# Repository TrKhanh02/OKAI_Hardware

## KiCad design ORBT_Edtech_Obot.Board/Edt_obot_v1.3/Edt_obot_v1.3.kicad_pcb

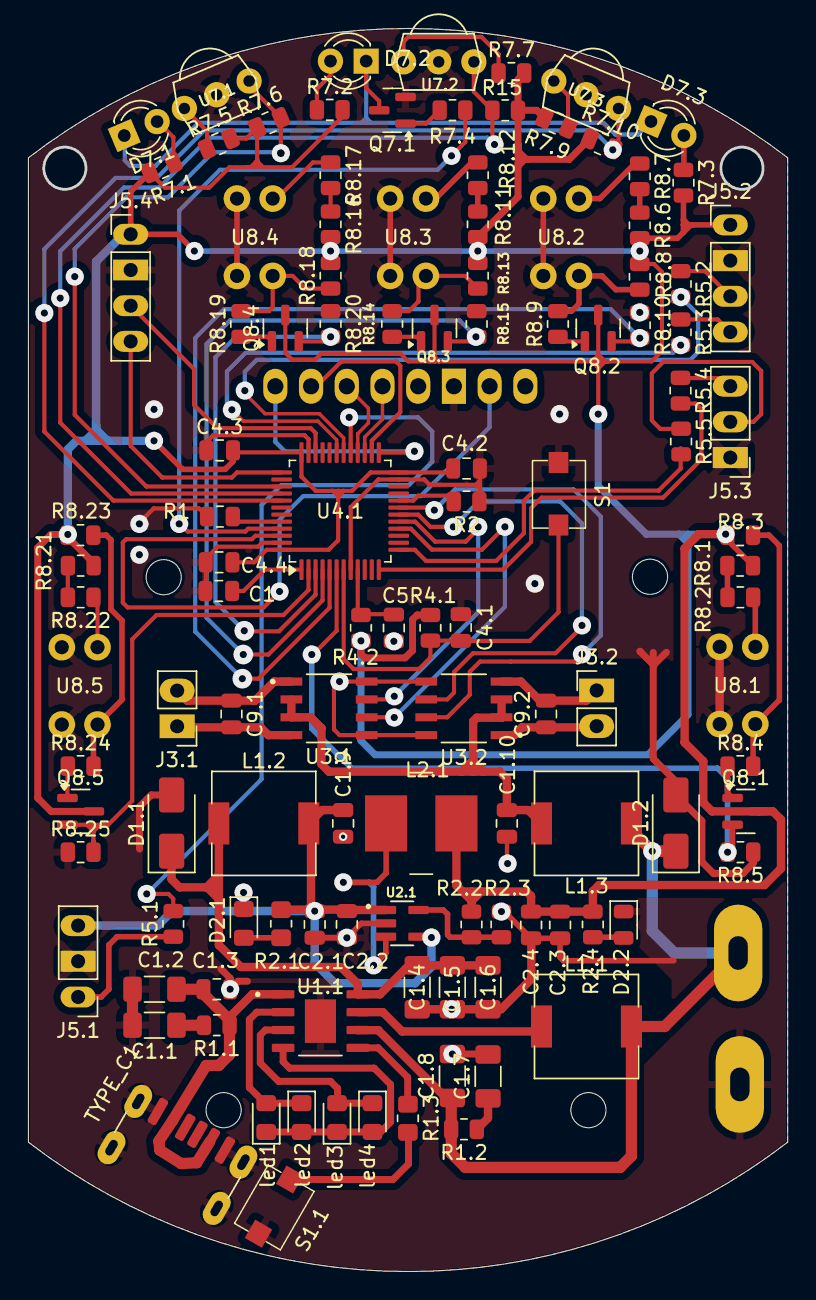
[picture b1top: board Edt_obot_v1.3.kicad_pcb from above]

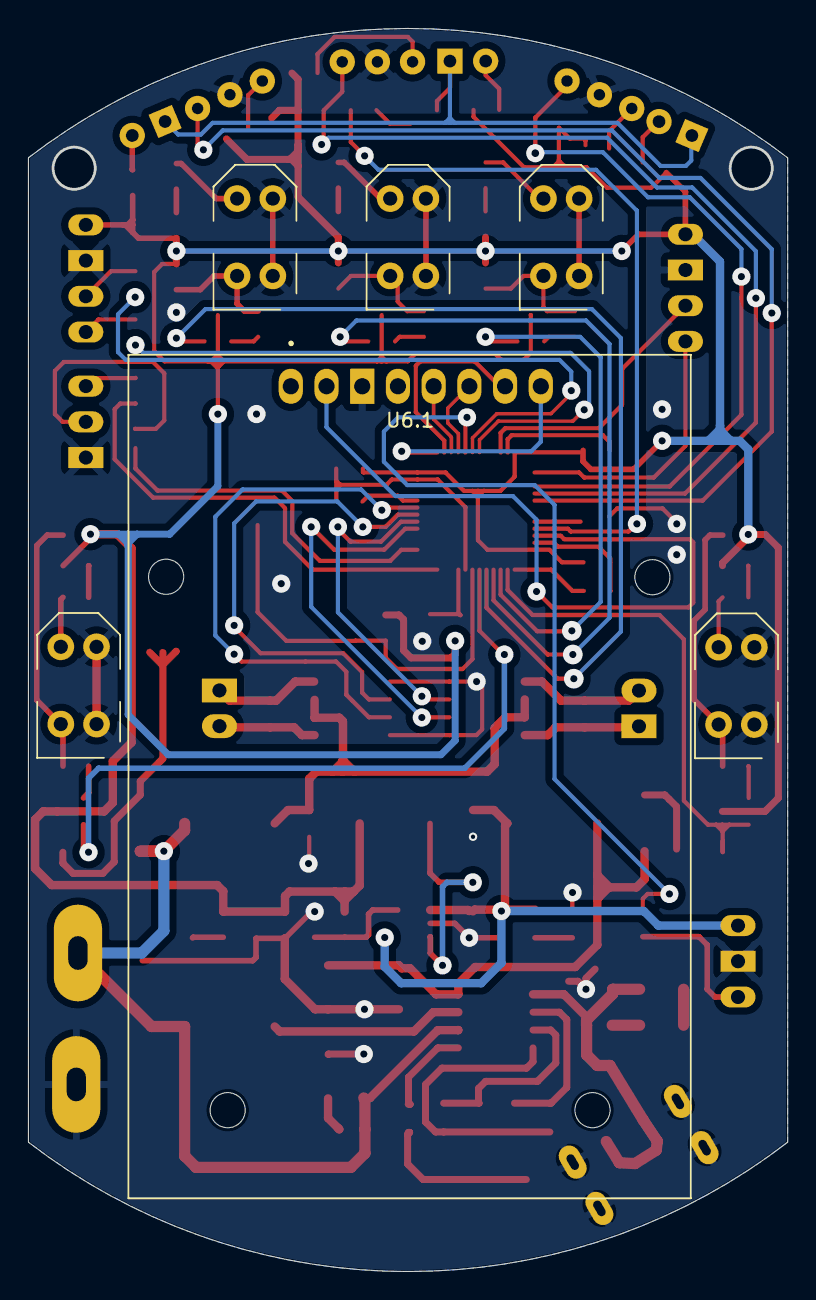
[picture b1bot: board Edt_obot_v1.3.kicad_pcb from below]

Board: 2 copper layers, 54.0 x 88.4 mm, 117 parts (6 on the bottom side), 86 nets.

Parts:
C1, C1.3, C4.1, C4.2, C4.3, C4.4, C5, C9.1, C9.2: 104; C_0805_2012Metric
C1.1, C1.2: 106; C_1206_3216Metric_Pad1.33x1.80mm_HandSolder
C1.4, C1.5, C1.6: 22 UF; C_1206_3216Metric_Pad1.33x1.80mm_HandSolder
C1.7: 22uf; C_1206_3216Metric_Pad1.33x1.80mm_HandSolder
C1.8: 22uF; C_1206_3216Metric_Pad1.33x1.80mm_HandSolder
C1.9, C1.10, C2.1, C2.4: 10uF; C_0805_2012Metric
C2.2, C2.3: 0.1uF; C_0805_2012Metric
D1.1, D1.2: SS34; D_SMA
D2.1: LED_Small_Filled; LED_0805_2012Metric_Pad1.15x1.40mm_HandSolder
D2.2: LED; LED_0805_2012Metric
D7.1, D7.2, D7.3: IR7393C; LED_D3.0mm_IRBlack
J3.1: MT1; PinHeader_1x02_P2.54mm_Vertical
J3.2: MT2; PinHeader_1x02_P2.54mm_Vertical
J5.1: LED; PinHeader_1x03_P2.54mm_Vertical
J5.2: UART_Debug; PinHeader_1x04_P2.54mm_Vertical
J5.3: UART_ESP; PinHeader_1x03_P2.54mm_Vertical
J5.4: Bootloader; PinHeader_1x04_P2.54mm_Vertical
L1.1: 1R; L_7.3x7.3_H4.5
L1.2, L1.3: L; L_7.3x7.3_H4.5
L2.1: 22uH; L_Ferrocore_DLG-0705
Q7.1, Q8.1, Q8.2, Q8.3, Q8.4, Q8.5: SS8050; SOT-23
R1, R2, R2.2, R4.1, R7.1, R7.2, R7.3, R7.6, R7.10, R8.3, R8.5, R8.8, R8.10, R8.13, R8.15, R8.18, R8.20, R8.23, R8.25: 10K; R_0805_2012Metric
R1.1, R1.2: 2R; R_0805_2012Metric
R1.3: 10k; R_0805_2012Metric_Pad1.20x1.40mm_HandSolder
R2.1: 1K; R_0805_2012Metric_Pad1.20x1.40mm_HandSolder
R2.3: 2.2K; R_0805_2012Metric
R2.4, R7.4, R8.4, R8.9, R8.14, R8.19, R8.24: 1K; R_0805_2012Metric
R4.2, R5.1, R5.2, R5.3, R5.4, R5.5: 0R; R_0805_2012Metric
R7.5, R7.7, R7.9: 100R; R_0805_2012Metric
R8.1, R8.2: 150R; R_0805_2012Metric
R8.6, R8.7, R8.11, R8.12, R8.16, R8.17, R8.21, R8.22: 680R; R_0805_2012Metric
R15: R7.8; R_0805_2012Metric
S1: RST; SW_TS10-63-26-BE-250-SMT-TR
S1.1: TS10-63-26-BE-250-SMT-TR; SW_TS10-63-26-BE-250-SMT-TR
TYPE_C1: USB_C_Receptacle_PowerOnly_6P; USB_C_Receptacle_GCT_USB4125-xx-x_6P_TopMnt_Horizontal
U1.1: IP5306; SOP127P600X165-9N
U2.1: TLV62569PDDCR; SOT95P280X110-6N
U3.1, U3.2: L9110S; SOIC127P599X172-8N
U4.1: CH32V203CxTx; LQFP-48_7x7mm_P0.5mm
U6.1: RFID; MODULE_CEG006900
U7.1, U7.2, U7.3: TSOP1838; TSOP18XX
U8.1, U8.2, U8.3, U8.4, U8.5: TCRT5000; OPTO_TCRT5000
led1: <25; LED_0805_2012Metric_Pad1.15x1.40mm_HandSolder
led2: <50; LED_0805_2012Metric_Pad1.15x1.40mm_HandSolder
led3: <75; LED_0805_2012Metric_Pad1.15x1.40mm_HandSolder
led4: >75; LED_0805_2012Metric_Pad1.15x1.40mm_HandSolder

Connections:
+3.3V: C2.3.1, C2.4.1, C4.2.2, C4.3.2, C4.4.2, J5.2.1, J5.4.1, L2.1.1, Q8.1.3 (C), Q8.2.3 (C), Q8.3.3 (C), Q8.4.3 (C), Q8.5.3 (C), R2.2.2, R2.4.2, R4.1.1, R4.2.2, R7.1.2, R7.2.2, R7.3.2, R7.5.2, R7.6.1, R7.7.2, R7.9.2, R7.10.1, R8.1.2, R8.3.2, R8.6.2, R8.8.2, R8.11.2, R8.13.2, R8.16.2, R8.18.2, R8.21.2, R8.23.2, R15.1, U4.1.24 (VDD_VIO_1), U4.1.36 (VDD_2), U4.1.48 (VDD_VIO_3)
/2: U1.1.2 (LED1), led1.2 (A), led2.1 (K)
/3: U1.1.3 (LED2), led3.2 (A), led4.1 (K)
/3V7_BAT: C1.8.1, D1.2.1 (K), L1.1.2, L1.3.1, R1.2.2, U1.1.6 (BAT)
/4: U1.1.4 (LED3), led1.1 (K), led2.2 (A), led3.1 (K), led4.2 (A)
/5V: C1.9.2, C2.1.1, C2.2.1, J5.1.3, L1.2.2, R2.1.1, U2.1.1 (EN), U2.1.4 (VIN)
/5V_BAT: C1.4.2, C1.5.2, C1.6.2, D1.1.1 (K), L1.2.1, U1.1.8 (VOUT)
/5V_USB: C1.2.1, C1.3.1, R1.1.2, TYPE_C1.A9 (VBUS), TYPE_C1.B9 (VBUS), U1.1.1 (VIN)
/BOOT0: R1.2, U4.1.44 (BOOT0)
/BOOT1: R2.2, U4.1.20 (PB2/BOOT1)
/CS/SDA: U4.1.25 (PB12), U6.1.8 (SS/SDA/RX)
/FB_U1.1: R2.2.1, R2.3.2, U2.1.6 (FB)
/IA1: U3.1.6 (IA), U4.1.16 (PA6)
/IA2: U3.2.6 (IA), U4.1.18 (PB0)
/IB1: U3.1.7 (IB), U4.1.17 (PA7)
/IB2: U3.2.7 (IB), U4.1.19 (PB1)
/IR1: R7.6.2, U4.1.39 (PB3), U7.1.OUT
/IR2: R15.2, U4.1.40 (PB4), U7.2.OUT
/IR3: R7.10.2, U4.1.41 (PB5), U7.3.OUT
/LINE1: Q8.1.2 (E), R8.5.2, U4.1.6 (OSC_OUT/PD1)
/LINE2: Q8.2.2 (E), R8.10.2, U4.1.5 (OSC_IN/PD0)
/LINE3: Q8.3.2 (E), R8.15.2, U4.1.4 (PC15-OSC32_OUT)
/LINE4: Q8.4.2 (E), R8.20.2, U4.1.3 (PC14-OSC32_IN)
/LINE5: Q8.5.2 (E), R8.25.2, U4.1.2 (PC13-TAMPER-RTC)
/MISO: U4.1.27 (PB14), U6.1.5 (MISO/SCL/TX)
/MOSI: U4.1.28 (PB15), U6.1.6 (MOSI)
/OA1: C9.1.1, J3.1.2, U3.1.1 (OA)
/OA2: C9.2.1, J3.2.2, U3.2.1 (OA)
/OB1: C9.1.2, J3.1.1, U3.1.4 (OB)
/OB2: C9.2.2, J3.2.1, U3.2.4 (OB)
/PA2: R5.4.2, U4.1.12 (PA2)
/PA3: R5.5.2, U4.1.13 (PA3)
/PA8: R5.1.2, U4.1.29 (PA8)
/PA9: R5.2.2, U4.1.30 (PA9)
/PA10: R5.3.2, U4.1.31 (PA10)
/PA13: J5.4.3, U4.1.34 (PA13/SWDIO)
/PA14: J5.4.4, U4.1.37 (PA14/SWCLK)
/PB8: R7.4.2, U4.1.45 (PB8)
/PB9: U4.1.46 (PB9), U6.1.2 (RST)
/PB13: U4.1.26 (PB13), U6.1.7 (SCK)
/RX_Debug: J5.2.4, R5.3.1
/RX_ESP: J5.3.2, R5.5.1
/SENSE: C1.7.1, R1.2.1
/TX_Debug: J5.2.3, R5.2.1
/TX_ESP: J5.3.3, R5.4.1
/VDDA: C5.2, R4.2.1, U4.1.9 (VDDA)
/WS2812: J5.1.1, R5.1.1
GND: C1.2, C1.1.2, C1.2.2, C1.3.2, C1.4.1, C1.5.1, C1.6.1, C1.7.2, C1.8.2, C1.9.1, C1.10.1, C2.1.2, C2.2.2, C2.3.2, C2.4.2, C4.1.2, C4.2.1, C4.3.1, C4.4.1, C5.1, D1.1.2 (A), D1.2.2 (A), D2.1.1 (K), D2.2.1 (K), J5.1.2, J5.2.2, J5.3.1, J5.4.2, Q7.1.2 (E), R1.1, R2.1, R2.3.1, R8.5.1, R8.10.1, R8.15.1, R8.20.1, R8.25.1, S1.1, S1.1.2, TYPE_C1.A12 (GND), TYPE_C1.B12 (GND), TYPE_C1.S1 (SHIELD), U1.1.9 (POWERPAD), U2.1.2 (GND), U3.1.5 (GND), U3.1.8 (GND), U3.2.5 (GND), U3.2.8 (GND), U4.1.8 (VSSA), U4.1.23 (VSS), U4.1.35 (VSS), U4.1.47 (VSS), U6.1.3 (GND), U7.1.GND, U7.2.GND, U7.3.GND, U8.1.CATH, U8.1.E, U8.2.CATH, U8.2.E, U8.3.CATH, U8.3.E, U8.4.CATH, U8.4.E, U8.5.CATH, U8.5.E
unnamed: C1.1.1, R1.1.1
unnamed: D2.1.2 (A), R2.1.2
unnamed: D2.2.2 (A), R2.4.1
unnamed: D7.1.2 (A), R7.1.1
unnamed: D7.1.1 (K), D7.2.1 (K), D7.3.1 (K), Q7.1.3 (C)
unnamed: D7.2.2 (A), R7.2.1
unnamed: D7.3.2 (A), R7.3.1
unnamed: Q7.1.1 (B), R7.4.1
unnamed: Q8.1.1 (B), R8.4.1
unnamed: Q8.2.1 (B), R8.9.1
unnamed: Q8.3.1 (B), R8.14.1
unnamed: Q8.4.1 (B), R8.19.1
unnamed: Q8.5.1 (B), R8.24.1
unnamed: R1.3.2, S1.1.1
unnamed: R8.1.1, R8.2.2
unnamed: R8.2.1, U8.1.A
unnamed: R8.3.1, R8.4.2, U8.1.COLL
unnamed: R8.6.1, R8.7.2
unnamed: R8.7.1, U8.2.A
unnamed: R8.8.1, R8.9.2, U8.2.COLL
unnamed: R8.11.1, R8.12.2
unnamed: R8.12.1, U8.3.A
unnamed: R8.13.1, R8.14.2, U8.3.COLL
unnamed: R8.16.1, R8.17.2
unnamed: R8.17.1, U8.4.A
unnamed: R8.18.1, R8.19.2, U8.4.COLL
unnamed: R8.21.1, R8.22.2
unnamed: R8.22.1, U8.5.A
unnamed: R8.23.1, R8.24.2, U8.5.COLL
unnamed: R1.3.1, U1.1.5 (KEY)
unnamed: L1.1.1, U1.1.7 (SW)
unnamed: L2.1.2, U2.1.3 (SW)
unnamed: C1.1, U4.1.1 (VBAT)
unnamed: C4.1.1, R4.1.2, S1.2, U4.1.7 (~RST)
unnamed: R7.5.1, U7.1.VCC (V+)
unnamed: R7.7.1, U7.2.VCC (V+)
unnamed: R7.9.1, U7.3.VCC (V+)
VCC: C1.10.2, L1.3.2, U3.1.2 (VCC), U3.1.3 (VCC), U3.2.2 (VCC), U3.2.3 (VCC)

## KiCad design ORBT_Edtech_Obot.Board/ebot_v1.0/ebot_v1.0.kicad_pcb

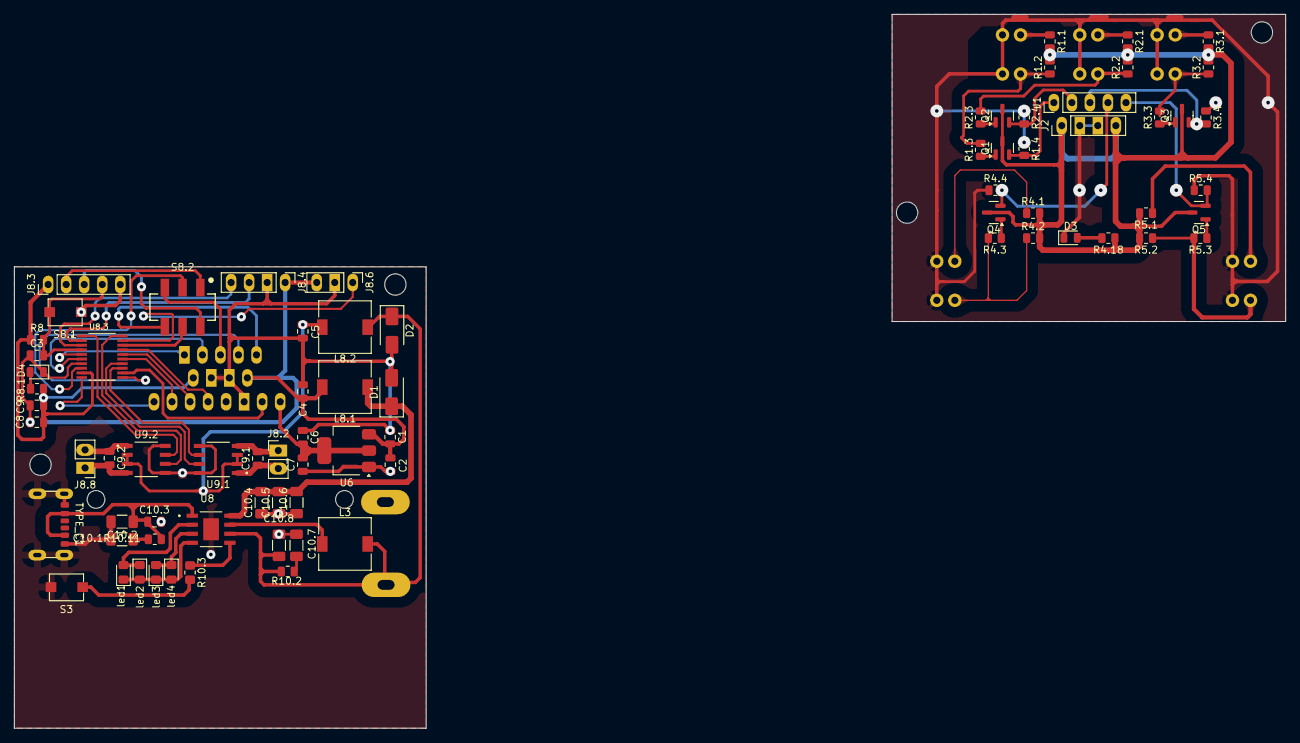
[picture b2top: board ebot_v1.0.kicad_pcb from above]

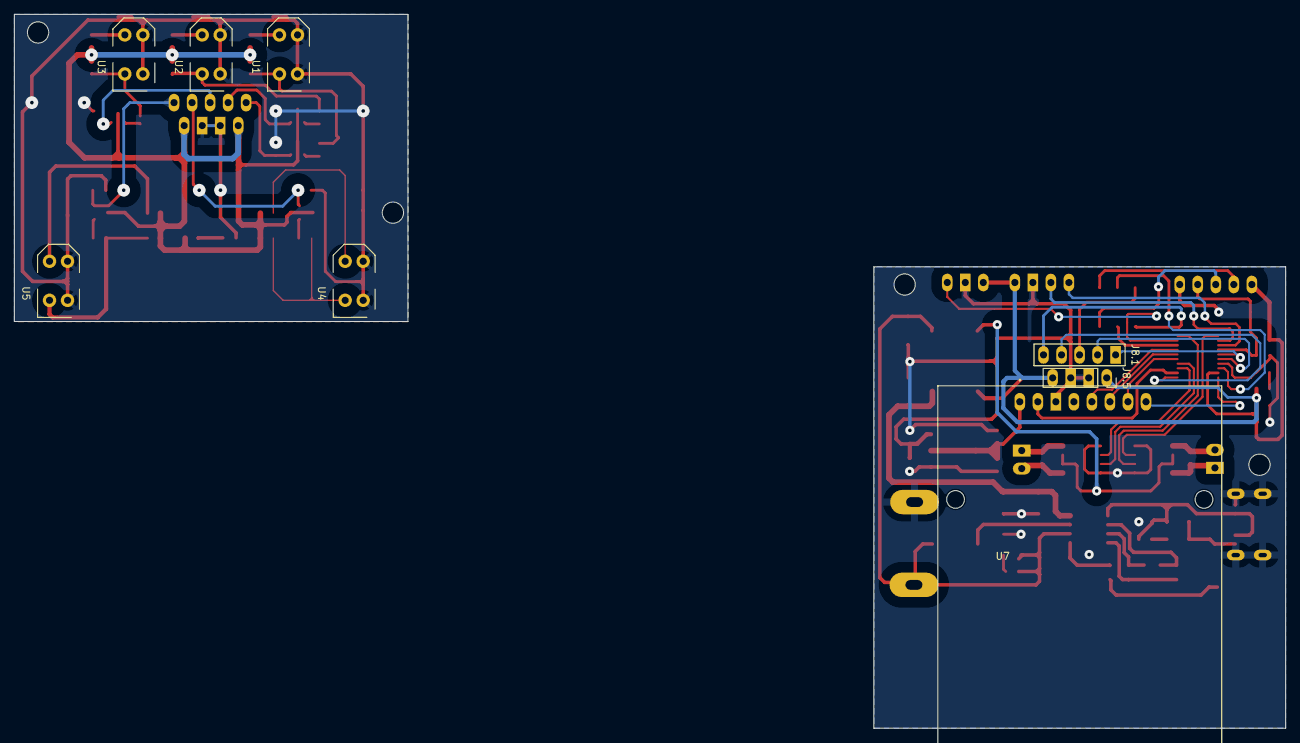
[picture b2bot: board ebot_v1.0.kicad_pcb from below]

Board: 2 copper layers, 179.1 x 100.6 mm, 85 parts (8 on the bottom side), 65 nets.

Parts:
C1, C3, C4, C5, C6, C9: 10uF; C_0805_2012Metric
C2, C7, C8, C9.1, C9.2, C10.3: 104; C_0805_2012Metric
C10.1, C10.2: 106; C_1206_3216Metric_Pad1.33x1.80mm_HandSolder
C10.4, C10.5, C10.6: 22 UF; C_1206_3216Metric_Pad1.33x1.80mm_HandSolder
C10.7: 22uf; C_1206_3216Metric_Pad1.33x1.80mm_HandSolder
C10.8: 22uF; C_1206_3216Metric_Pad1.33x1.80mm_HandSolder
D1, D2: SS34; D_SMA
D3, D4: LED; LED_0805_2012Metric
J1: IR_LINE; PinHeader_1x05_P2.54mm_Vertical
J2: IR_LINE; PinHeader_1x04_P2.54mm_Vertical
J8.1: Conn_01x05_Pin; PinSocket_1x05_P2.54mm_Vertical
J8.2, J8.8: MT2; PinHeader_1x02_P2.54mm_Vertical
J8.3: UPLOAD; PinHeader_1x05_P2.54mm_Vertical
J8.4: UART; PinHeader_1x04_P2.54mm_Vertical
J8.5: NGUON; PinSocket_1x04_P2.54mm_Vertical
J8.6: LED; PinHeader_1x03_P2.54mm_Vertical
L3: 1R; L_7.3x7.3_H4.5
L8.1, L8.2: L; L_7.3x7.3_H4.5
Q1, Q2, Q3, Q4, Q5: SS8050; SOT-23
R1.1, R3.1, R4.1, R4.18, R5.1: 150R; R_0805_2012Metric
R1.2, R1.4, R3.2, R3.4, R4.2, R4.4, R5.2, R5.4: 6.2k; R_0805_2012Metric
R1.3, R2.3, R3.3, R4.3, R5.3: 1K; R_0805_2012Metric
R2.1: 680R; R_0805_2012Metric
R2.2, R2.4, R8: 10K; R_0805_2012Metric
R8.1: 1k; R_0805_2012Metric
R10.2, R10.11: 2R; R_0805_2012Metric
R10.3: 10k; R_0805_2012Metric_Pad1.20x1.40mm_HandSolder
S3: TS10-63-26-BE-250-SMT-TR; SW_TS10-63-26-BE-250-SMT-TR
S8.1: RST; SW_TS10-63-26-BE-250-SMT-TR
S8.2: 452406020024
TYPE_C1: USB_C_Receptacle_PowerOnly_6P; USB_C_Receptacle_GCT_USB4125-xx-x_6P_TopMnt_Horizontal
U1, U2, U3, U4, U5: TCRT5000; OPTO_TCRT5000
U6: AMS1117-3.3; SOT-223-3_TabPin2
U7: RFID; MODULE_CEG006900
U8: IP5306; SOP127P600X165-9N
U8.3: N76E003AT20; SOP65P640X120-20N
U9.1, U9.2: L9110S; SOIC127P599X172-8N
led1: <25; LED_0805_2012Metric_Pad1.15x1.40mm_HandSolder
led2: <50; LED_0805_2012Metric_Pad1.15x1.40mm_HandSolder
led3: <75; LED_0805_2012Metric_Pad1.15x1.40mm_HandSolder
led4: >75; LED_0805_2012Metric_Pad1.15x1.40mm_HandSolder

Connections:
+5V: J2.1, J2.4, Q1.3 (C), Q2.3 (C), Q3.3 (C), Q4.3 (C), Q5.3 (C), R1.1.2, R1.2.2, R2.1.2, R2.2.2, R3.1.2, R3.2.2, R4.1.2, R4.2.2, R4.18.1, R5.1.2, R5.2.2
/2: U8.2 (LED1), led1.2 (A), led2.1 (K)
/3: U8.3 (LED2), led3.2 (A), led4.1 (K)
/3V3: C6.2, C7.2, U6.2 (VO), U7.1 (VCC)
/3V7_BAT: C10.8.1, D2.1 (K), L3.2, L8.2.1, R10.2.2, U8.6 (BAT)
/4: U8.4 (LED3), led1.1 (K), led2.2 (A), led3.1 (K), led4.2 (A)
/5V: C1.2, C2.2, C4.2, C8.2, C9.2, J8.3.1, J8.4.1, J8.5.1, J8.5.4, J8.6.3, L8.1.2, R8.1, R8.1.1, U6.3 (VI), U8.3.9 (VDD)
/5V_BAT: C10.4.2, C10.5.2, C10.6.2, D1.1 (K), L8.1.1, U8.8 (VOUT)
/5V_USB: C10.2.1, C10.3.1, R10.11.2, TYPE_C1.A9 (VBUS), TYPE_C1.B9 (VBUS), U8.1 (VIN)
/IA1: U8.3.13 (P1.2/PWM0/IC0), U9.1.6 (IA)
/IA2: U8.3.20 (P0.4/AIN5/STADC/PWM3/IC3), U9.2.6 (IA)
/IB1: U8.3.14 (P1.1/PWM1/IC1/AIN7/CLO), U9.1.7 (IB)
/IB2: U8.3.1 (P0.5/PWM2/IC6/T0/AIN4), U9.2.7 (IB)
/IR_LINE1: J1.1, Q1.2 (E), R1.4.2
/IR_LINE2: J1.2, Q2.2 (E), R2.4.2
/IR_LINE3: J1.3, Q3.2 (E), R3.4.2
/IR_LINE4: J1.4, Q4.2 (E), R4.4.2
/IR_LINE5: J1.5, Q5.2 (E), R5.4.2
/LINE1: J8.1.1, U8.3.5 (P3.0/~INT0/OSCIN/AIN1)
/LINE2: J8.1.2, U8.3.6 (P1.7/~INT1/AIN0)
/LINE3: J8.1.3, S8.2.3
/LINE4: J8.1.4, U8.3.11 (P1.4/SDA/FB/PWM1)
/LINE5: J8.1.5, S8.2.6
/MISO: U7.5 (MISO/SCL/TX), U8.3.17 (P0.1/PWM4/IC4/MISO)
/MOSI: U7.6 (MOSI), U8.3.16 (P0.0/PWM3/IC3/MOSI/T1)
/OA1: C9.1.1, J8.2.2, U9.1.1 (OA)
/OA2: C9.2.1, J8.8.2, U9.2.1 (OA)
/OB1: C9.1.2, J8.2.1, U9.1.4 (OB)
/OB2: C9.2.2, J8.8.1, U9.2.4 (OB)
/P02: S8.2.5, U8.3.18 (P0.2/ICPCK/OCDCK/RXD_1/[SCL])
/P16: S8.2.2, U8.3.8 (P1.6/[SDA]/TXD_1/ICPDA/OCDDA)
/RC1: C10.1.1, R10.11.1
/RST: C3.2, J8.3.4, R8.2, S8.1.2, U8.3.4 (P2.0/~RST)
/RST_RFID: U7.2 (RST), U8.3.12 (P1.3/SCL/[STADC])
/RX: J8.4.4, U8.3.3 (P0.7/RXD/AIN2)
/RX1: J8.3.3, S8.2.4
/SENSE: C10.7.1, R10.2.1
/SLK: U7.7 (SCK), U8.3.15 (P1.0/PWM2/IC2/SPCLK)
/SS: U7.8 (SS/SDA/RX), U8.3.10 (P1.5/PWM5/IC7/~SS)
/TX: J8.4.3, U8.3.2 (P0.6/TXD/AIN3)
/TX1: J8.3.2, S8.2.1
/WS2812: J8.6.1, U8.3.19 (P0.3/PWM5/IC5/AIN6)
GND: C1.1, C2.1, C3.1, C4.1, C5.1, C6.1, C7.1, C8.1, C9.1, C10.1.2, C10.2.2, C10.3.2, C10.4.1, C10.5.1, C10.6.1, C10.7.2, C10.8.2, D1.2 (A), D2.2 (A), D4.1 (K), J8.3.5, J8.4.2, J8.5.2, J8.5.3, J8.6.2, S3.2, S8.1.1, TYPE_C1.A12 (GND), TYPE_C1.B12 (GND), TYPE_C1.S1 (SHIELD), U6.1 (GND), U7.3 (GND), U8.9 (POWERPAD), U8.3.7 (GND), U9.1.5 (GND), U9.1.8 (GND), U9.2.5 (GND), U9.2.8 (GND)
GND0: D3.1 (K), J2.2, J2.3, R1.4.1, R2.4.1, R3.4.1, R4.4.1, R5.4.1, U1.CATH, U1.E, U2.CATH, U2.E, U3.CATH, U3.E, U4.CATH, U4.E, U5.CATH, U5.E
unnamed: D3.2 (A), R4.18.2
unnamed: D4.2 (A), R8.1.2
unnamed: Q1.1 (B), R1.3.1
unnamed: Q2.1 (B), R2.3.1
unnamed: Q3.1 (B), R3.3.1
unnamed: Q4.1 (B), R4.3.1
unnamed: Q5.1 (B), R5.3.1
unnamed: R1.1.1, U1.A
unnamed: R1.2.1, R1.3.2, U1.COLL
unnamed: R2.1.1, U2.A
unnamed: R2.2.1, R2.3.2, U2.COLL
unnamed: R3.1.1, U3.A
unnamed: R3.2.1, R3.3.2, U3.COLL
unnamed: R4.1.1, U4.A
unnamed: R4.2.1, R4.3.2, U4.COLL
unnamed: R5.1.1, U5.A
unnamed: R5.2.1, R5.3.2, U5.COLL
unnamed: R10.3.2, S3.1
unnamed: R10.3.1, U8.5 (KEY)
unnamed: L3.1, U8.7 (SW)
VCC: C5.2, L8.2.2, U9.1.2 (VCC), U9.1.3 (VCC), U9.2.2 (VCC), U9.2.3 (VCC)

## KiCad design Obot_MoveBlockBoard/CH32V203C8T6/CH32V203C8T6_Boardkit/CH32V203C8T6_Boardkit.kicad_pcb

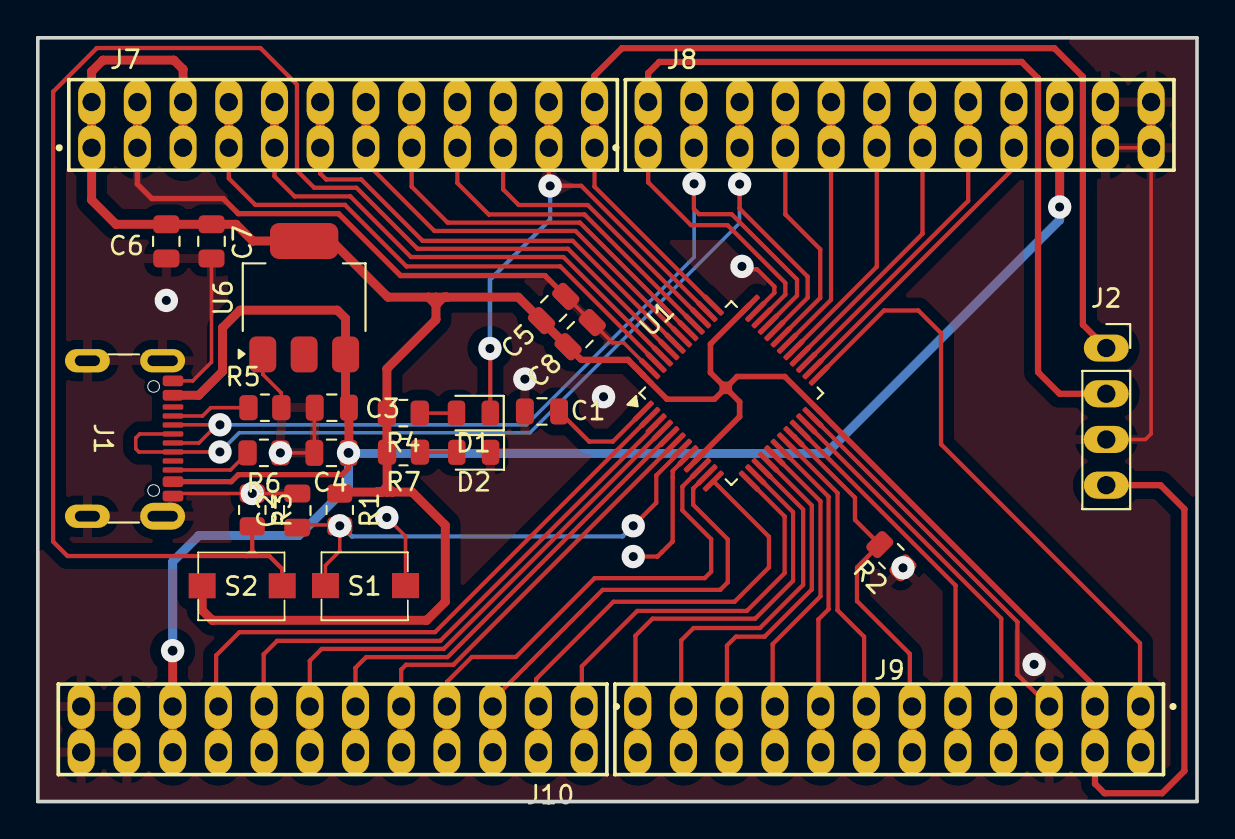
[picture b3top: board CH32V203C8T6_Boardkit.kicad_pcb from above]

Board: 2 copper layers, 64.4 x 42.4 mm, 27 parts (0 on the bottom side), 47 nets.

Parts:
C1, C2, C4, C5, C7, C8: 104; C_0805_2012Metric
C3: 106; C_0805_2012Metric
C6: 10uF; C_0805_2012Metric
D1, D2: LED; LED_0805_2012Metric
J1: USB_C_Receptacle_USB2.0_16P; USB_C_Receptacle_GCT_USB4105-xx-A_16P_TopMnt_Horizontal
J2: BOOTLOADER; PinSocket_1x04_P2.54mm_Vertical
J7, J8, J9, J10: MTSW-112-X-X-D-X; SAMTEC_MTSW-112-X-X-D-X
R1, R2, R3, R4, R7: 10K; R_0805_2012Metric
R5, R6: 5.6K; R_0805_2012Metric
S1: RST; SW_TS10-63-26-BE-250-SMT-TR
S2: BOOT_USB; SW_TS10-63-26-BE-250-SMT-TR
U1: CH32V203CxTx; LQFP-48_7x7mm_P0.5mm
U6: AMS1117-3.3; SOT-223-3_TabPin2

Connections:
+3.3V: C5.2, C6.2, C7.2, C8.2, J2.4, J7.01, J7.02, J7.05, J7.06, J9.03, J9.04, R1.1, R4.2, R7.2, S2.2, U1.9 (VDDA), U1.24 (VDD_VIO_1), U1.36 (VDD_2), U1.48 (VDD_VIO_3), U6.2 (VO)
/5V_USB: C3.2, C4.2, J1.A4 (VBUS), J1.A9 (VBUS), J1.B4 (VBUS), J1.B9 (VBUS), J8.19, J8.20, J10.19, J10.20, U6.3 (VI)
/BOOT0: R3.2, S2.1, U1.44 (BOOT0)
/BOOT1: J9.11, J9.12, R2.2, U1.20 (PB2/BOOT1)
/PA0: J10.07, J10.08, U1.10 (PA0-WUKP)
/PA1: J10.05, J10.06, U1.11 (PA1)
/PA2: J10.03, J10.04, U1.12 (PA2)
/PA3: J10.01, J10.02, U1.13 (PA3)
/PA4: J9.23, J9.24, U1.14 (PA4)
/PA5: J9.21, J9.22, U1.15 (PA5)
/PA6: J9.19, J9.20, U1.16 (PA6)
/PA7: J9.17, J9.18, U1.17 (PA7)
/PA8: J8.11, J8.12, U1.29 (PA8)
/PA9: J8.09, J8.10, U1.30 (PA9)
/PA10: J8.07, J8.08, U1.31 (PA10)
/PA11: J1.A6 (D+), J1.B6 (D+), J8.05, J8.06, U1.32 (PA11/USB1DM)
/PA12: J1.A7 (D-), J1.B7 (D-), J8.03, J8.04, U1.33 (PA12/USB1DP)
/PA13: J2.2, J8.01, J8.02, U1.34 (PA13/SWDIO)
/PA14: J2.1, J7.23, J7.24, U1.37 (PA14/SWCLK)
/PA15: D1.1 (K), J7.21, J7.22, U1.38 (PA15)
/PB0: J9.15, J9.16, U1.18 (PB0)
/PB1: J9.13, J9.14, U1.19 (PB1)
/PB3: J7.19, J7.20, U1.39 (PB3)
/PB4: J7.17, J7.18, U1.40 (PB4)
/PB5: J7.15, J7.16, U1.41 (PB5)
/PB6: J7.13, J7.14, U1.42 (PB6/USB2DM)
/PB7: J7.11, J7.12, U1.43 (PB7/USB2DP)
/PB8: J7.09, J7.10, U1.45 (PB8)
/PB9: J7.07, J7.08, U1.46 (PB9)
/PB10: J9.09, J9.10, U1.21 (PB10)
/PB11: J9.07, J9.08, U1.22 (PB11)
/PB12: J9.01, J9.02, U1.25 (PB12)
/PB13: J8.17, J8.18, U1.26 (PB13)
/PB14: J8.15, J8.16, U1.27 (PB14)
/PB15: J8.13, J8.14, U1.28 (PB15)
/PC13: J10.17, J10.18, U1.2 (PC13-TAMPER-RTC)
/PC14: J10.15, J10.16, U1.3 (PC14-OSC32_IN)
/PC15: J10.13, J10.14, U1.4 (PC15-OSC32_OUT)
/PD0: J10.11, J10.12, U1.5 (OSC_IN/PD0)
/PD1: J10.09, J10.10, U1.6 (OSC_OUT/PD1)
GND: C1.2, C2.2, C3.1, C4.1, C5.1, C6.1, C7.1, C8.1, D2.1 (K), J1.A1 (GND), J1.A12 (GND), J1.B1 (GND), J1.B12 (GND), J1.S1 (SHIELD), J2.3, J7.03, J7.04, J8.21, J8.22, J8.23, J8.24, J9.05, J9.06, J10.21, J10.22, J10.23, J10.24, R2.1, R3.1, R5.2, R6.2, S1.1, U1.8 (VSSA), U1.23 (VSS), U1.35 (VSS), U1.47 (VSS), U6.1 (GND)
unnamed: D1.2 (A), R4.1
unnamed: D2.2 (A), R7.1
unnamed: J1.A5 (CC1), R5.1
unnamed: J1.B5 (CC2), R6.1
unnamed: C1.1, U1.1 (VBAT)
unnamed: C2.1, R1.2, S1.2, U1.7 (~RST)
